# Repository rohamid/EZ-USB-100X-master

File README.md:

# EZ USB FX2LP 100X
EZ USB FX2LP CY7C68013A 100pin Development board

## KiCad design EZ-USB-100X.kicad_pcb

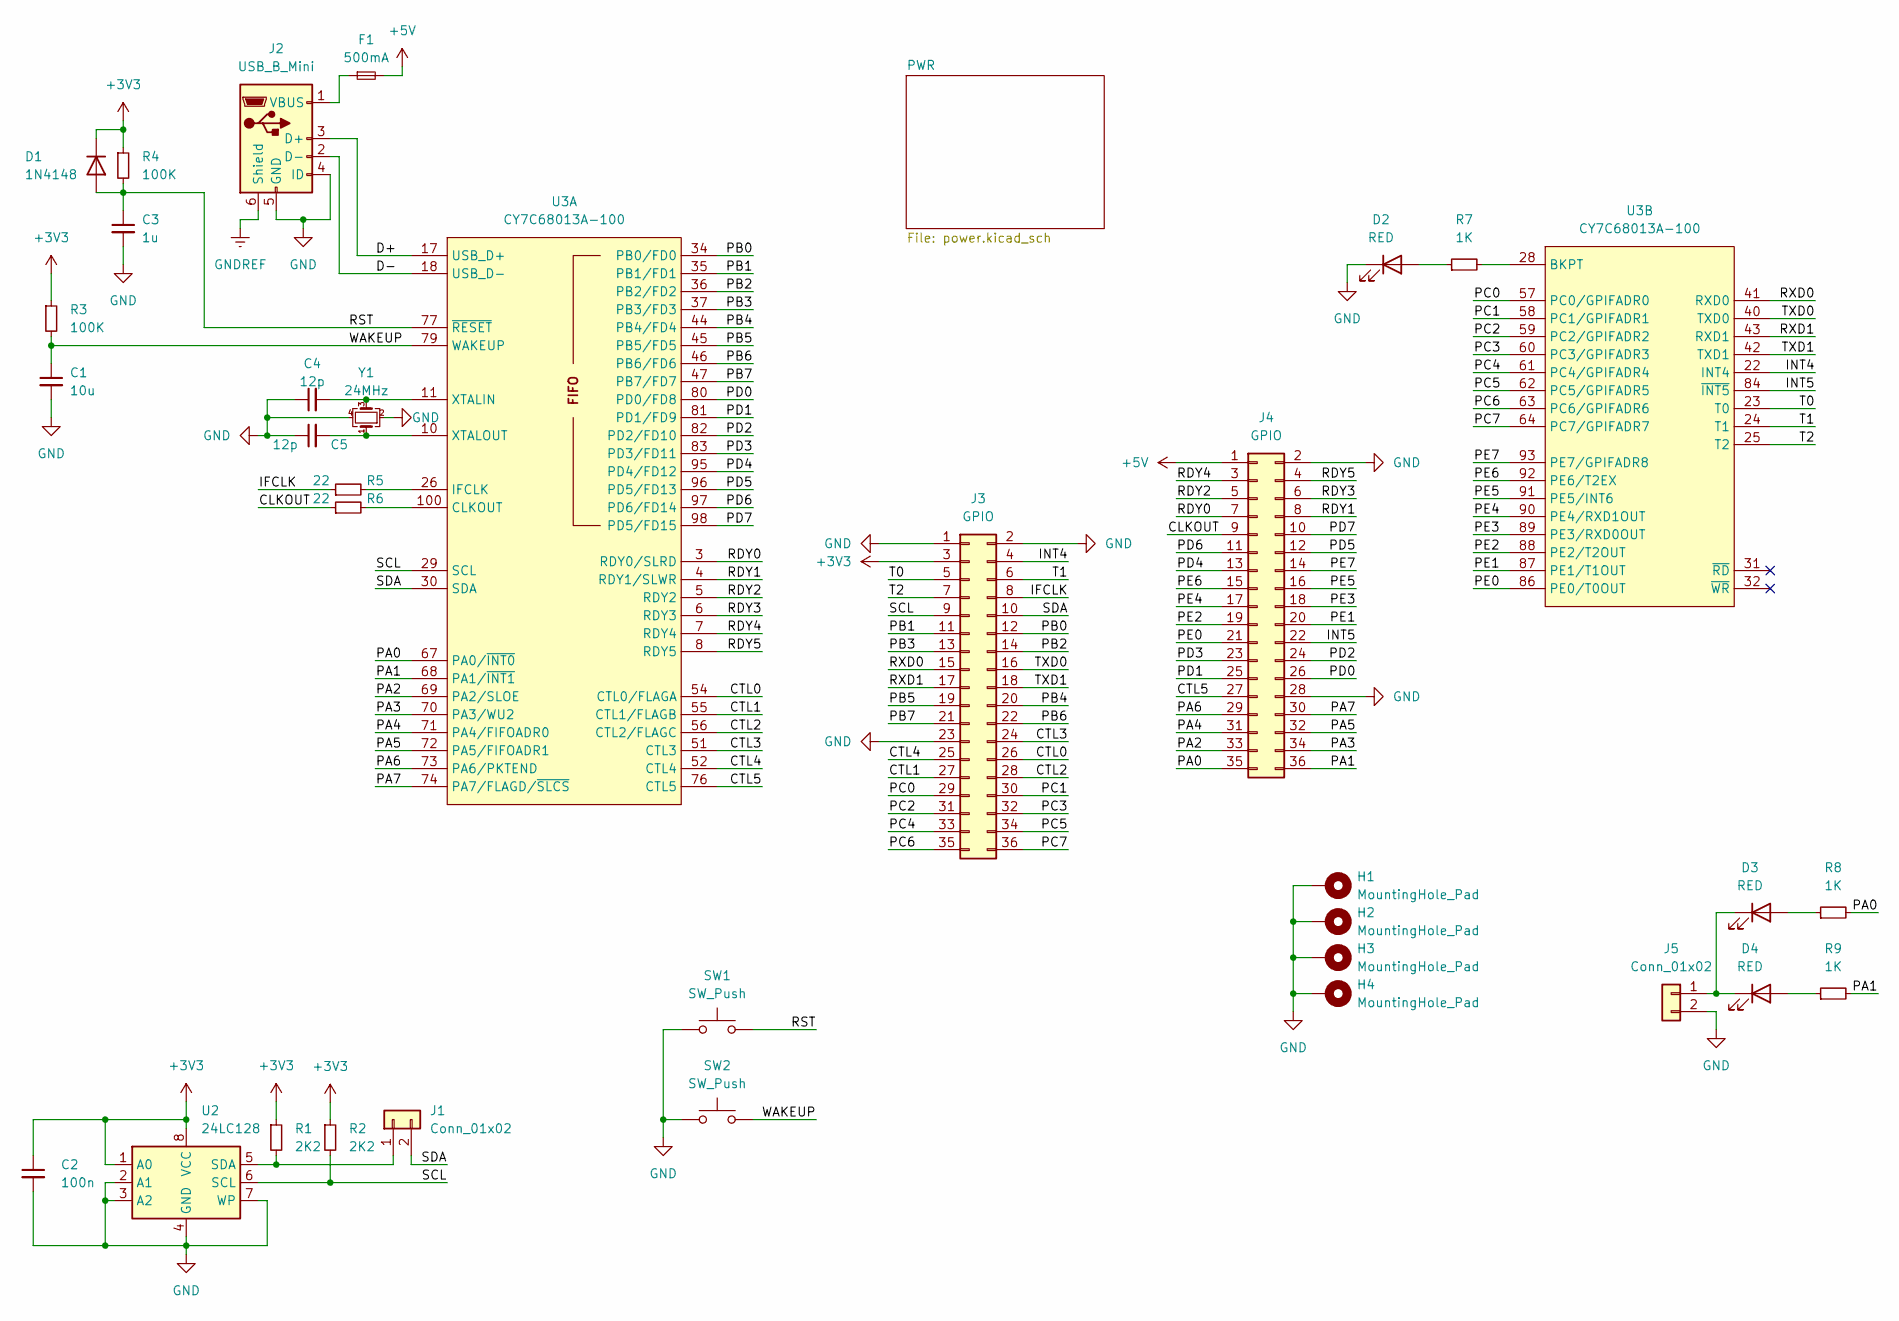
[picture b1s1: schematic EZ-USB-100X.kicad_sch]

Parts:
C1: 10u; C_0402_1005Metric; LCSC Part Number C15525
C2: 100n; C_0402_1005Metric; LCSC Part Number C307331
C3: 1u; C_0402_1005Metric; LCSC Part Number C52923
C4, C5: 12p; C_0402_1005Metric; LCSC Part Number C1547
D1: 1N4148; D_SOD-123; LCSC Part Number C81598
D2, D3, D4: RED; LED_0805_2012Metric; LCSC Part Number C84256
F1: 500mA; Fuse_0805_2012Metric; LCSC Part Number C269104
H1, H2, H3, H4: MountingHole_Pad; MountingHole_3.2mm_M3_Pad_Via
J1, J5: Conn_01x02; PinHeader_1x02_P2.54mm_Vertical
J2: USB_B_Mini; USB_Mini-B_Lumberg_2486_01_Horizontal; LCSC Part Number C508689
J3, J4: GPIO; PinHeader_2x18_P2.54mm_Vertical
R1, R2: 2K2; R_0402_1005Metric; LCSC Part Number C25879
R3, R4: 100K; R_0402_1005Metric; LCSC Part Number C25741
R5, R6: 22; R_0402_1005Metric; LCSC Part Number C25092
R7, R8, R9: 1K; R_0402_1005Metric; LCSC Part Number C11702
SW1, SW2: SW_Push; SW_SPST_PTS810; LCSC Part Number C127488
U2: 24LC128; SOIC-8_3.9x4.9mm_P1.27mm; LCSC Part Number C99368
U3: CY7C68013A-100; PQFP-100_14x20mm_P0.65mm; LCSC Part Number C9926
Y1: 24MHz; Crystal_SMD_3225-4Pin_3.2x2.5mm; LCSC Part Number C2650460

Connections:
+3V3: C2.1, D1.1 (K), J3.3, R1.1, R2.1, R3.1, R4.1, U2.1 (A0), U2.8 (VCC); also elsewhere on the board
+5V: F1.2, J4.1; also elsewhere on the board
/CLKOUT: J4.9, R6.1
/CTL0: J3.26, U3.54 (CTL0/FLAGA)
/CTL1: J3.27, U3.55 (CTL1/FLAGB)
/CTL2: J3.28, U3.56 (CTL2/FLAGC)
/CTL3: J3.24, U3.51 (CTL3)
/CTL4: J3.25, U3.52 (CTL4)
/CTL5: J4.27, U3.76 (CTL5)
/D+: J2.3 (D+), U3.17 (USB_D+)
/D-: J2.2 (D-), U3.18 (USB_D-)
/IFCLK: J3.8, R5.1
/INT4: J3.4, U3.22 (INT4)
/INT5: J4.22, U3.84 (~INT5)
/PA0: J4.35, R8.2, U3.67 (PA0/~INT0)
/PA1: J4.36, R9.2, U3.68 (PA1/~INT1)
/PA2: J4.33, U3.69 (PA2/SLOE)
/PA3: J4.34, U3.70 (PA3/WU2)
/PA4: J4.31, U3.71 (PA4/FIFOADR0)
/PA5: J4.32, U3.72 (PA5/FIFOADR1)
/PA6: J4.29, U3.73 (PA6/PKTEND)
/PA7: J4.30, U3.74 (PA7/FLAGD/~SLCS)
/PB0: J3.12, U3.34 (PB0/FD0)
/PB1: J3.11, U3.35 (PB1/FD1)
/PB2: J3.14, U3.36 (PB2/FD2)
/PB3: J3.13, U3.37 (PB3/FD3)
/PB4: J3.20, U3.44 (PB4/FD4)
/PB5: J3.19, U3.45 (PB5/FD5)
/PB6: J3.22, U3.46 (PB6/FD6)
/PB7: J3.21, U3.47 (PB7/FD7)
/PC0: J3.29, U3.57 (PC0/GPIFADR0)
/PC1: J3.30, U3.58 (PC1/GPIFADR1)
/PC2: J3.31, U3.59 (PC2/GPIFADR2)
/PC3: J3.32, U3.60 (PC3/GPIFADR3)
/PC4: J3.33, U3.61 (PC4/GPIFADR4)
/PC5: J3.34, U3.62 (PC5/GPIFADR5)
/PC6: J3.35, U3.63 (PC6/GPIFADR6)
/PC7: J3.36, U3.64 (PC7/GPIFADR7)
/PD0: J4.26, U3.80 (PD0/FD8)
/PD1: J4.25, U3.81 (PD1/FD9)
/PD2: J4.24, U3.82 (PD2/FD10)
/PD3: J4.23, U3.83 (PD3/FD11)
/PD4: J4.13, U3.95 (PD4/FD12)
/PD5: J4.12, U3.96 (PD5/FD13)
/PD6: J4.11, U3.97 (PD6/FD14)
/PD7: J4.10, U3.98 (PD5/FD15)
/PE0: J4.21, U3.86 (PE0/T0OUT)
/PE1: J4.20, U3.87 (PE1/T1OUT)
/PE2: J4.19, U3.88 (PE2/T2OUT)
/PE3: J4.18, U3.89 (PE3/RXD0OUT)
/PE4: J4.17, U3.90 (PE4/RXD1OUT)
/PE5: J4.16, U3.91 (PE5/INT6)
/PE6: J4.15, U3.92 (PE6/T2EX)
/PE7: J4.14, U3.93 (PE7/GPIFADR8)
/RDY0: J4.7, U3.3 (RDY0/SLRD)
/RDY1: J4.8, U3.4 (RDY1/SLWR)
/RDY2: J4.5, U3.5 (RDY2)
/RDY3: J4.6, U3.6 (RDY3)
/RDY4: J4.3, U3.7 (RDY4)
/RDY5: J4.4, U3.8 (RDY5)
/RST: C3.1, D1.2 (A), R4.2, SW1.2, U3.77 (~RESET)
/RXD0: J3.15, U3.41 (RXD0)
/RXD1: J3.17, U3.43 (RXD1)
/SCL: J3.9, R2.2, U2.6 (SCL), U3.29 (SCL)
/SDA: J1.2, J3.10, U3.30 (SDA)
/T0: J3.5, U3.23 (T0)
/T1: J3.6, U3.24 (T1)
/T2: J3.7, U3.25 (T2)
/TXD0: J3.16, U3.40 (TXD0)
/TXD1: J3.18, U3.42 (TXD1)
/WAKEUP: C1.1, R3.2, SW2.2, U3.79 (WAKEUP)
GND: C1.2, C2.2, C3.2, C4.1, C5.1, D2.1 (K), H1.1, H2.1, H3.1, H4.1, J2.4 (ID), J2.5 (GND), J3.1, J3.2, J3.23, J4.2, J4.28, J5.2, SW1.1, SW2.1, U2.2 (A1), U2.3 (A2), U2.4 (GND), U2.7 (WP), Y1.2, Y1.4; also elsewhere on the board
GNDREF: J2.6 (Shield); also elsewhere on the board
unnamed: D2.2 (A), R7.1
unnamed: D3.2 (A), R8.1
unnamed: D3.1 (K), D4.1 (K), J5.1
unnamed: D4.2 (A), R9.1
unnamed: J1.1, R1.2, U2.5 (SDA)
unnamed: F1.1, J2.1 (VBUS)
unnamed: R6.2, U3.100 (CLKOUT)
unnamed: R5.2, U3.26 (IFCLK)
unnamed: C4.2, U3.11 (XTALIN), Y1.3
unnamed: C5.2, U3.10 (XTALOUT), Y1.1
unnamed: R7.2, U3.28 (BKPT)

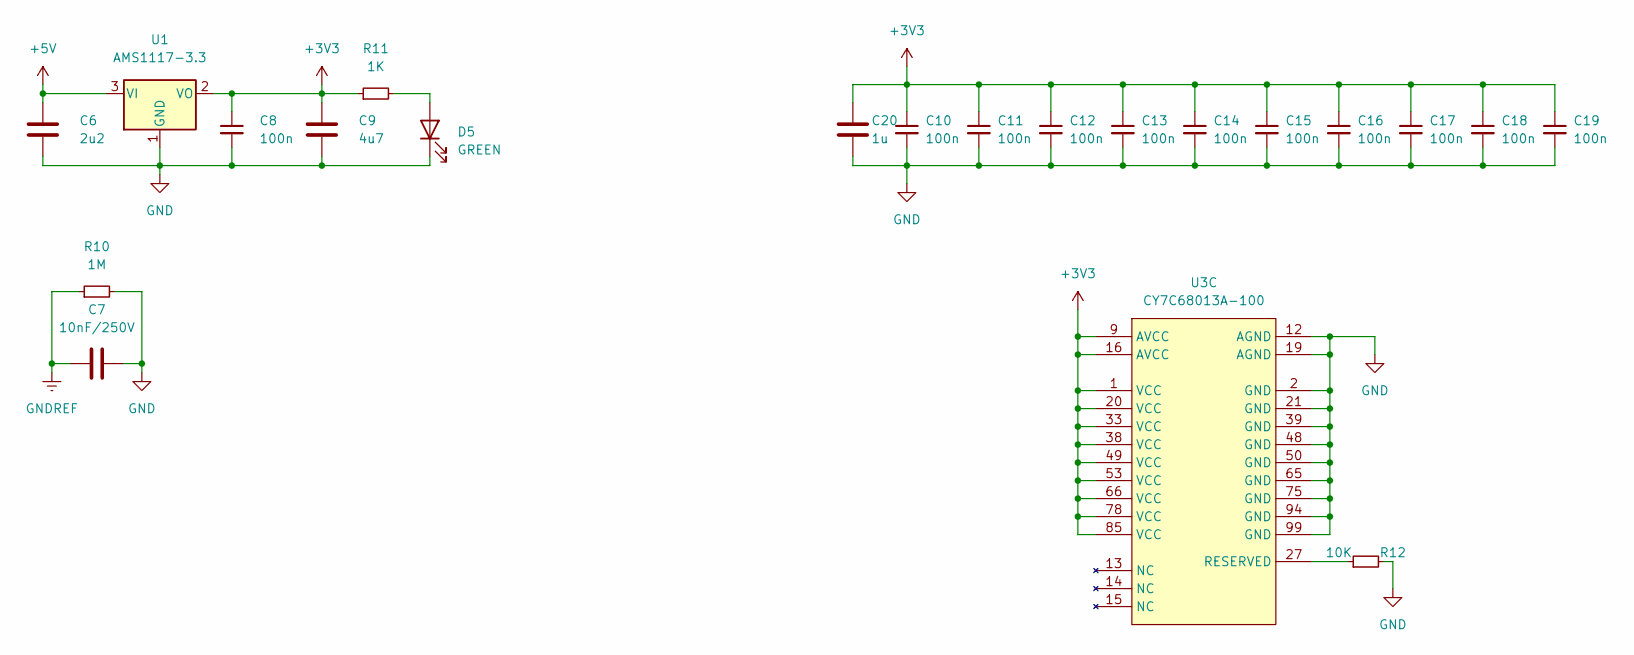
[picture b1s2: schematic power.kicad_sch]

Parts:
C6: 2u2; C_0805_2012Metric; LCSC Part Number C49217
C7: 10nF/250V; C_0603_1608Metric; LCSC Part Number C336636
C8, C10, C11, C12, C13, C14, C15, C16, C17, C18, C19: 100n; C_0402_1005Metric; LCSC Part Number C307331
C9: 4u7; C_0805_2012Metric; LCSC Part Number C1779
C20: 1u; C_0603_1608Metric; LCSC Part Number C15849
D5: GREEN; LED_0805_2012Metric; LCSC Part Number C2297
R10: 1M; R_0402_1005Metric; LCSC Part Number C26083
R11: 1K; R_0402_1005Metric; LCSC Part Number C11702
R12: 10K; R_0402_1005Metric; LCSC Part Number C25744
U1: AMS1117-3.3; SOT-223-3_TabPin2; LCSC Part Number C6186
U3: CY7C68013A-100; PQFP-100_14x20mm_P0.65mm; LCSC Part Number C9926

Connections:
+3V3: C8.1, C9.1, C10.1, C11.1, C12.1, C13.1, C14.1, C15.1, C16.1, C17.1, C18.1, C19.1, C20.1, R11.1, U1.2 (VO), U3.1 (VCC), U3.9 (AVCC), U3.16 (AVCC), U3.20 (VCC), U3.33 (VCC), U3.38 (VCC), U3.49 (VCC), U3.53 (VCC), U3.66 (VCC), U3.78 (VCC), U3.85 (VCC); also elsewhere on the board
+5V: C6.1, U1.3 (VI); also elsewhere on the board
GND: C6.2, C7.2, C8.2, C9.2, C10.2, C11.2, C12.2, C13.2, C14.2, C15.2, C16.2, C17.2, C18.2, C19.2, C20.2, D5.1 (K), R10.2, R12.2, U1.1 (GND), U3.2 (GND), U3.12 (AGND), U3.19 (AGND), U3.21 (GND), U3.39 (GND), U3.48 (GND), U3.50 (GND), U3.65 (GND), U3.75 (GND), U3.94 (GND), U3.99 (GND); also elsewhere on the board
GNDREF: C7.1, R10.1; also elsewhere on the board
unnamed: D5.2 (A), R11.2
unnamed: R12.1, U3.27 (RESERVED)

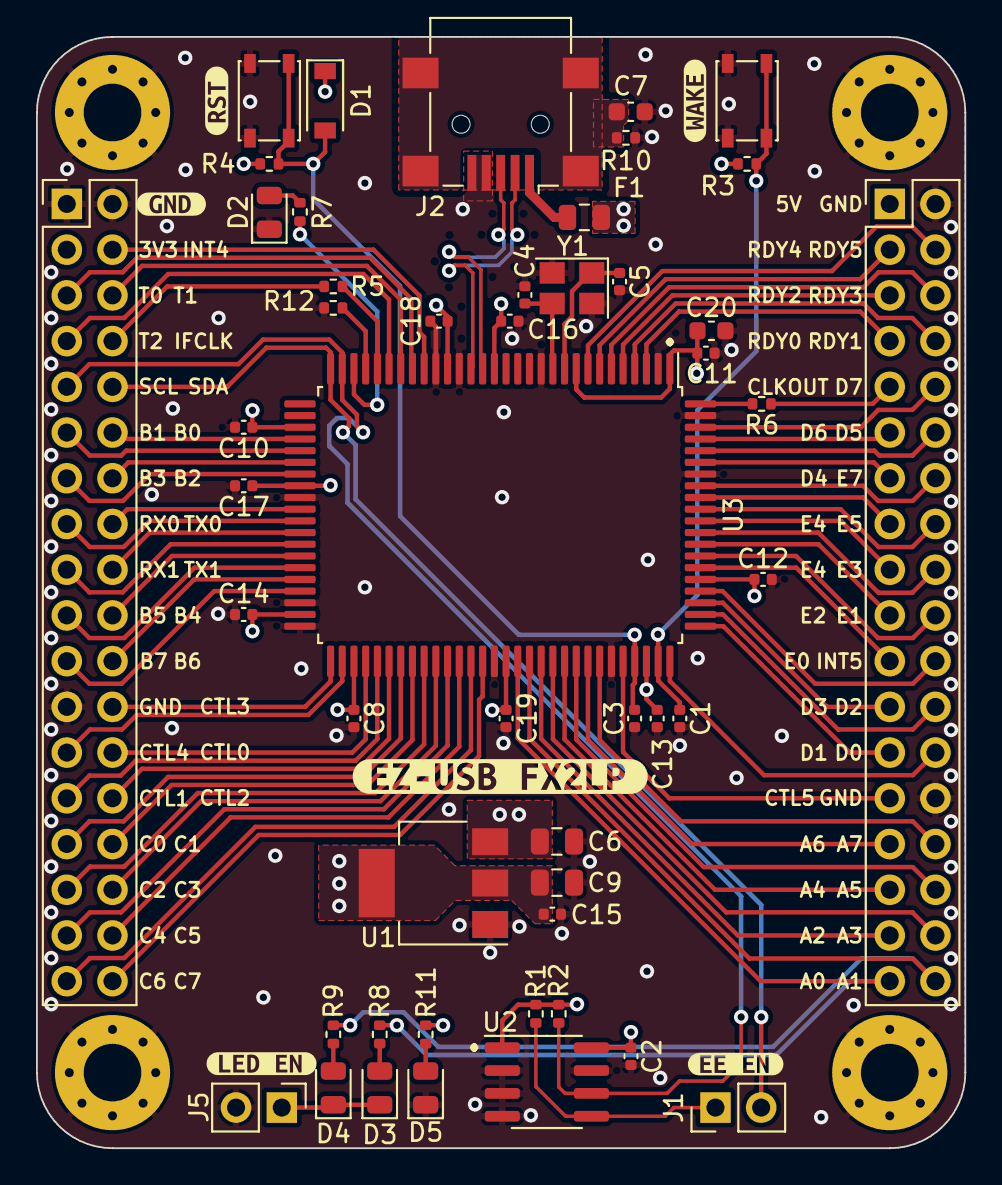
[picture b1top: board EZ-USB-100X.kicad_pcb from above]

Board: 4 copper layers, 51.6 x 61.7 mm, 60 parts (1 on the bottom side), 86 nets.

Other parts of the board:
kibuzzard-643CE35F: G***; kibuzzard-643CE35F
kibuzzard-643CE80E: G***; kibuzzard-643CE80E
kibuzzard-643CE364: G***; kibuzzard-643CE364
kibuzzard-643E3FB1: G***; kibuzzard-643E3FB1
kibuzzard-643E3FBD: G***; kibuzzard-643E3FBD
kibuzzard-64365B80, kibuzzard-64365B80#2: G***; kibuzzard-64365B80
